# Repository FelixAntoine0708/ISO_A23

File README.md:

# Robot-sumo-A23
Cours d'Integration et systeme ordinée

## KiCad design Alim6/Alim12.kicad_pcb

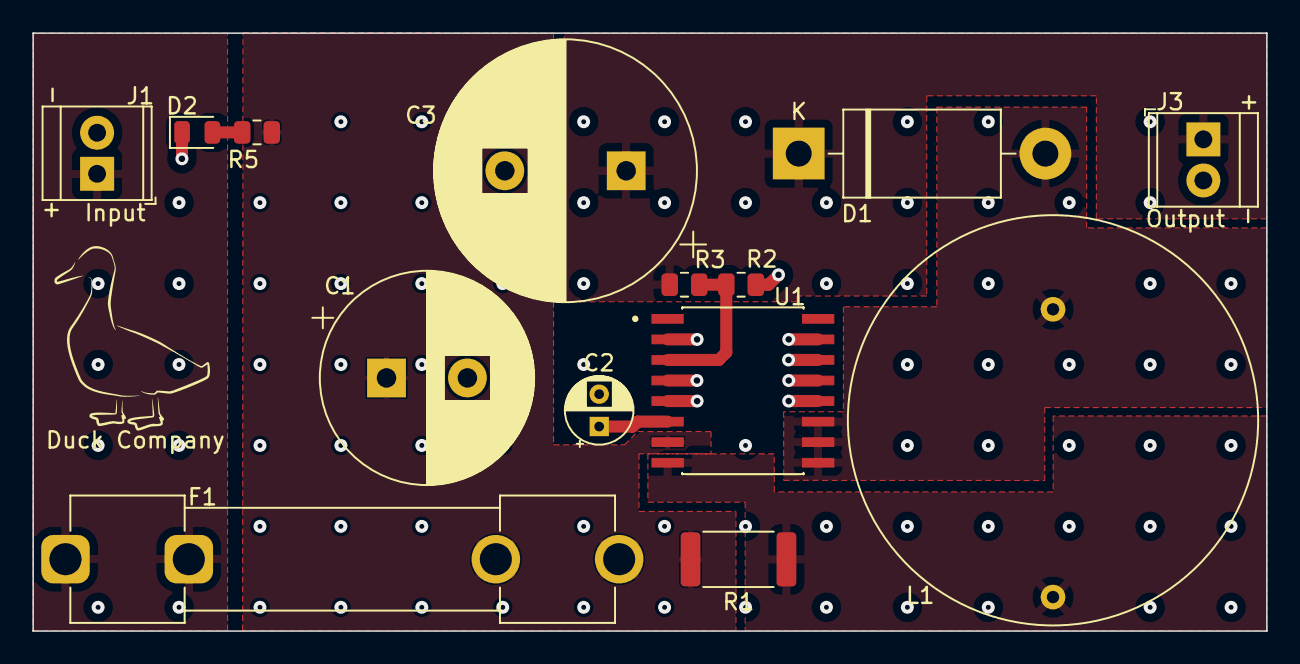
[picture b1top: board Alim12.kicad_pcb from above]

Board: 4 copper layers, 76.2 x 36.9 mm, 14 parts (0 on the bottom side), 9 nets.

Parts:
C1: Cin; CP_Radial_D13.0mm_P5.00mm
C2: Ct 680pF; CP_Radial_D4.0mm_P2.00mm
C3: Co; CP_Radial_D16.0mm_P7.50mm
D1: 1N5822; D_DO-201AD_P15.24mm_Horizontal
D2: LED; LED_0805_2012Metric
F1: Fuse; Fuseholder_Clip-6.3x32mm_Littelfuse_102_122_Inline_P34.21x7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
J1: Input; TerminalBlock_TE_282834-2_1x02_P2.54mm_Horizontal
J3: Output; TerminalBlock_TE_282834-2_1x02_P2.54mm_Horizontal
L1: 180nH; L0451-AL
R1: Rsc; R_2512_6332Metric
R2, R3: R_US; R_0805_2012Metric
R5: 10K; R_0805_2012Metric
U1: MC34163; SOIC127P1030X265-16N

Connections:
GND: C1.2, C2.2, C3.2, D2.1 (K), J1.2, J3.2, R2.2, U1.2 (Feedback_2), U1.4 (gnd), U1.5 (gnd), U1.12 (gnd), U1.13 (gnd), U1.14 (switch_E), U1.15 (switch_E)
unnamed: D1.2 (A), L1.2, U1.9 (driver), U1.10 (switch), U1.11 (switch)
unnamed: C3.1, D1.1 (K), J3.1, R3.2
unnamed: D2.2 (A), R5.2
unnamed: F1.1, J1.1
unnamed: R2.1, R3.1, U1.3 (Feedback_1)
unnamed: L1.1, R1.1, U1.8 (Ipk_Sense)
unnamed: C1.1, F1.2, R1.2, R5.1, U1.7 (VCC)
unnamed: C2.1, U1.6 (timing_capacitor)

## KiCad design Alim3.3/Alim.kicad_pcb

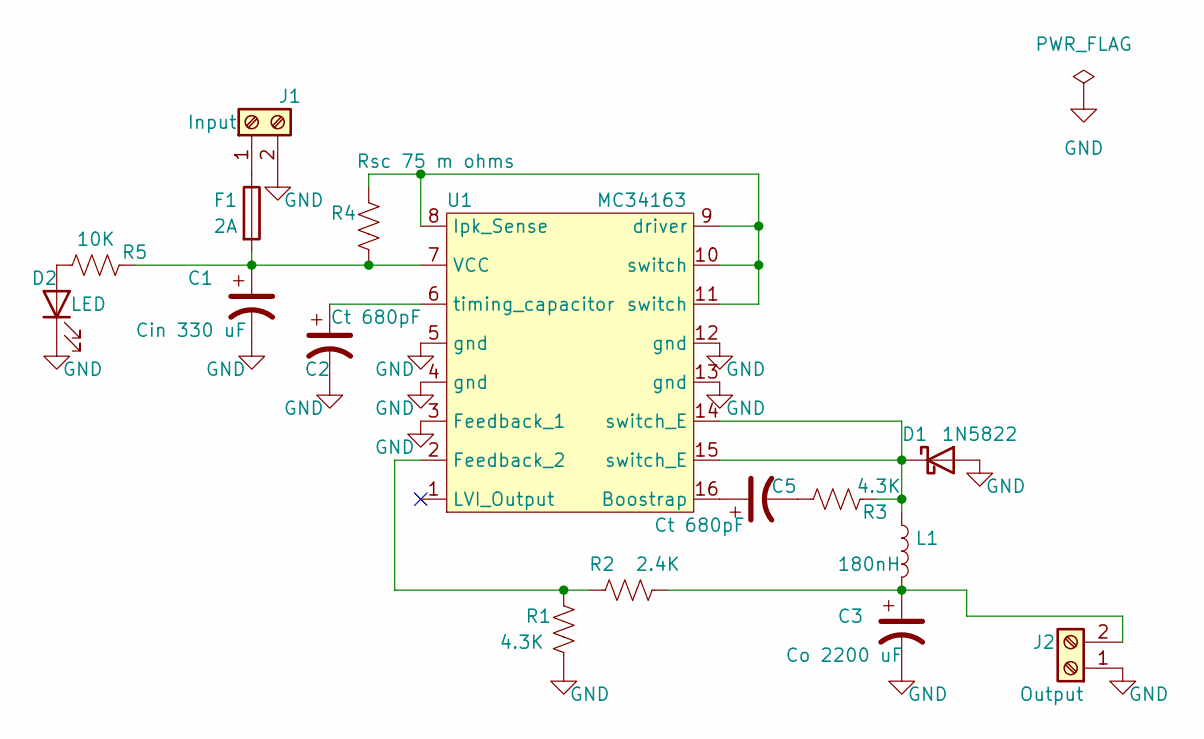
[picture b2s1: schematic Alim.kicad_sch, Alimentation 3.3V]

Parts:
C1: Cin 330 uF; CP_Radial_D13.0mm_P5.00mm
C2: Ct 680pF; CP_Radial_D4.0mm_P2.00mm
C3: Co 2200 uF; CP_Radial_D16.0mm_P7.50mm
C5: Ct 680pF; C_0805_2012Metric
D1: 1N5822; D_DO-201AD_P15.24mm_Horizontal
D2: LED; LED_0805_2012Metric
F1: 2A; Fuseholder_Clip-6.3x32mm_Littelfuse_102_122_Inline_P34.21x7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
J1: Input; TerminalBlock_TE_282834-2_1x02_P2.54mm_Horizontal
J2: Output; TerminalBlock_TE_282834-2_1x02_P2.54mm_Horizontal
L1: 180nH; L0451-AL
R1, R3: 4.3K; R_0805_2012Metric
R2: 2.4K; R_0805_2012Metric
R4: Rsc 75 m ohms; R_2512_6332Metric
R5: 10K; R_0805_2012Metric
U1: MC34163; MC34163-D

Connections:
GND: C1.2, C2.2, C3.2, D1.2 (A), D2.1 (K), J1.2, J2.1, R1.2, U1.3 (Feedback_1), U1.4 (gnd), U1.5 (gnd), U1.12 (gnd), U1.13 (gnd)
unnamed: C5.2, R3.1
unnamed: D1.1 (K), L1.1, R3.2, U1.14 (switch_E), U1.15 (switch_E)
unnamed: D2.2 (A), R5.1
unnamed: F1.1, J1.1
unnamed: C3.1, J2.2, L1.2, R2.2
unnamed: C5.1, U1.16 (Boostrap)
unnamed: R1.1, R2.1, U1.2 (Feedback_2)
unnamed: R4.1, U1.8 (Ipk_Sense), U1.9 (driver), U1.10 (switch), U1.11 (switch)
unnamed: C1.1, F1.2, R4.2, R5.2, U1.7 (VCC)
unnamed: C2.1, U1.6 (timing_capacitor)

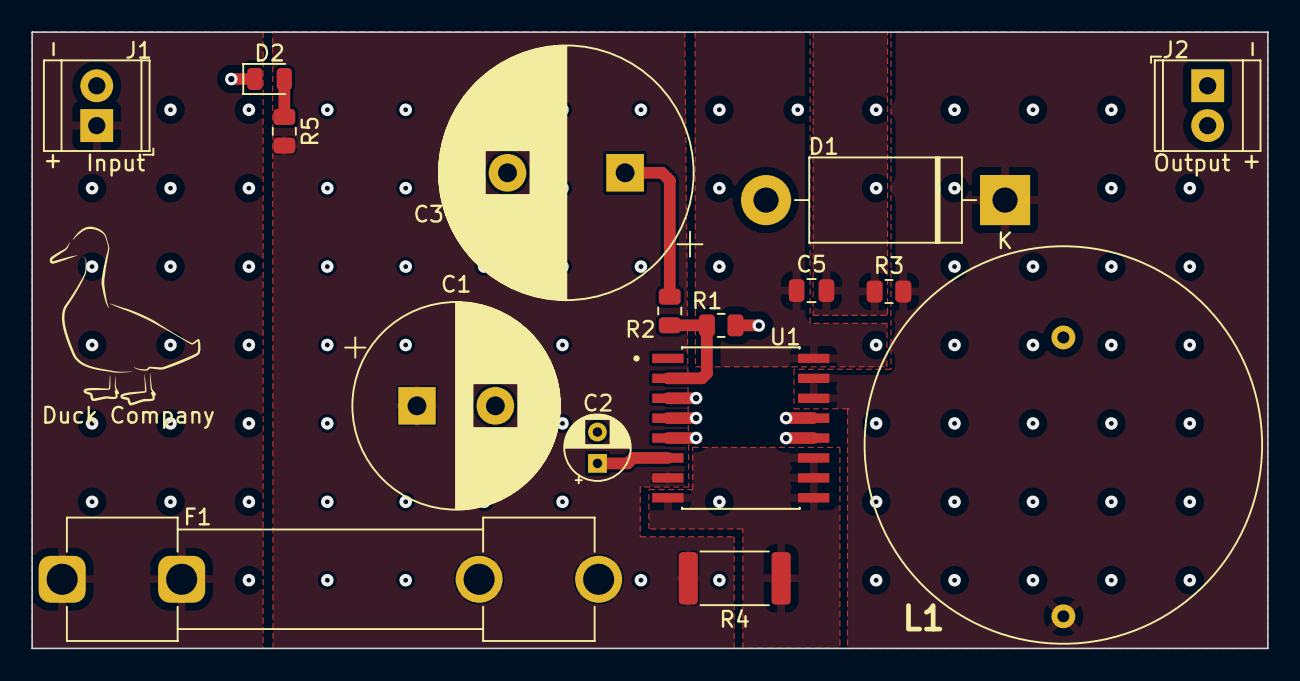
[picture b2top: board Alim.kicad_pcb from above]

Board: 4 copper layers, 78.8 x 39.3 mm, 16 parts (0 on the bottom side), 11 nets.

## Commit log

2023-09-19 File pour l'alim 3.3V
2023-09-19 File de l'alim 5V
2023-09-19 File pour l'alim 6V
2023-09-19 Gerber file du 3.3V
2023-09-19 Gerber file du 5V
2023-09-19 Gerber file du 6V
2023-09-28 wheel fonction forward
2023-11-01 Code du robot sumo
2023-11-01 wheel front-back code
2024-01-08 Model 3D du robot
2024-01-08 Code Robot Sumo
    Manque un petit décalage sur le capteur de ligne
2024-01-09 Code Final robot Sumo
